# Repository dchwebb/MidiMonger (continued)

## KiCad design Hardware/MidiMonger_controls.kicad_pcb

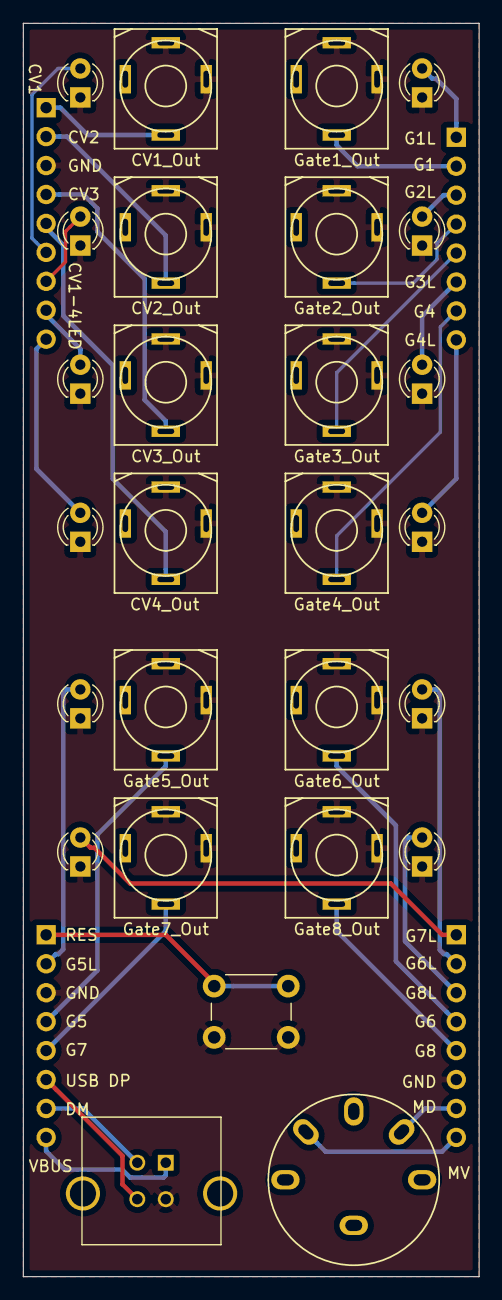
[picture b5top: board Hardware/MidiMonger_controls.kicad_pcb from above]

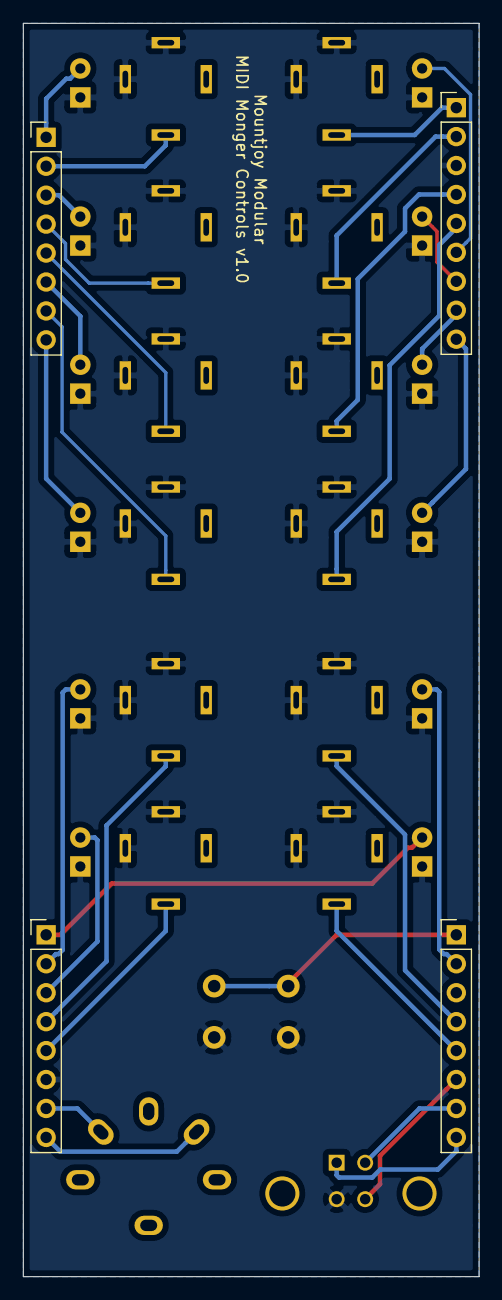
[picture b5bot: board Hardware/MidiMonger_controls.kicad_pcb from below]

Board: 2 copper layers, 40.0 x 110.0 mm, 31 parts (4 on the bottom side), 31 nets.

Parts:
D1: GATE1; LED_D3.0mm
D2: GATE2; LED_D3.0mm
D3: GATE3; LED_D3.0mm
D4: GATE4; LED_D3.0mm
D5: CV1; LED_D3.0mm
D6: CV2; LED_D3.0mm
D7: CV3; LED_D3.0mm
D8: CV4; LED_D3.0mm
D9: GATE5; LED_D3.0mm
D10: GATE6; LED_D3.0mm
D11: GATE7; LED_D3.0mm
D12: GATE8; LED_D3.0mm
J2: Gate3_Out; Cliff_3.5mm_Stereo_Jack
J3: Gate4_Out; Cliff_3.5mm_Stereo_Jack
J4: Gate1_Out; Cliff_3.5mm_Stereo_Jack
J5: Gate2_Out; Cliff_3.5mm_Stereo_Jack
J7: Gate5_Out; Cliff_3.5mm_Stereo_Jack
J8: Gate6_Out; Cliff_3.5mm_Stereo_Jack
J9: Gate7_Out; Cliff_3.5mm_Stereo_Jack
J10: Gate8_Out; Cliff_3.5mm_Stereo_Jack
J11: CV1_Out; Cliff_3.5mm_Stereo_Jack
J12: CV2_Out; Cliff_3.5mm_Stereo_Jack
J13: CV3_Out; Cliff_3.5mm_Stereo_Jack
J14: CV4_Out; Cliff_3.5mm_Stereo_Jack
J15: USB_B_Wurth
J16: MIDI_DIN
J20: Conn_01x09_Female; Socket_Strip_Straight_1x09_Pitch2.54mm
J21, J22, J23: Conn_01x08_Female; Socket_Strip_Straight_1x08_Pitch2.54mm
SW1: SW_Push; SW_PUSH_6mm

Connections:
CV1_LED_OUT: D5.2, J20.6
CV1_OUT: J11.3, J20.1
CV2_LED_OUT: D6.2, J20.7
CV2_OUT: J12.3, J20.2
CV3_LED_OUT: D7.2, J20.8
CV3_OUT: J13.3, J20.4
CV4_LED_OUT: D8.2, J20.9
CV4_OUT: J14.3, J20.5
GATE1_LED_OUT: D1.2, J21.1
GATE1_OUT: J4.3, J21.2
GATE2_LED_OUT: D2.2, J21.3
GATE2_OUT: J5.3, J21.4
GATE3_LED_OUT: D3.2, J21.6
GATE3_OUT: J2.3, J21.5
GATE4_LED_OUT: D4.2, J21.8
GATE4_OUT: J3.3, J21.7
GATE5_LED_OUT: D9.2, J22.2
GATE5_OUT: J7.3, J22.4
GATE6_LED_OUT: D10.2, J23.2
GATE6_OUT: J8.3, J23.4
GATE7_LED_OUT: D11.2, J23.1
GATE7_OUT: J9.3, J22.5
GATE8_LED_OUT: D12.2, J23.3
GATE8_OUT: J10.3, J23.5
GND: D1.1, D2.1, D3.1, D4.1, D5.1, D6.1, D7.1, D8.1, D9.1, D10.1, D11.1, D12.1, J2.1, J3.1, J4.1, J5.1, J7.1, J8.1, J9.1, J10.1, J11.1, J12.1, J13.1, J14.1, J15.4, J20.3, J22.3, J23.6, SW1.2
MIDI_DATA: J16.5, J23.7
MIDI_VREF: J16.4, J23.8
RESET_SWITCH: J22.1, SW1.1
USB_DM: J15.2, J22.7
USB_DP: J15.3, J22.6
USB_VBUS: J15.1, J22.8

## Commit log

2019-10-24 Removed apparently unused code from USB class
2019-10-24 Added handling for monophonic pitch and on/off handling via std::list
2019-10-28 Updates to web editor; added midi handler class
2019-10-30 Implemented basic external DAC support
2019-10-31 dacA data send
2019-11-01 Implemented software/hardware NSS for DAC and moved initialisation to DAC class
2019-11-01 CV out to external DAC
2019-11-04 Updates to configuration message exchange; schematic revised to include gate output
2019-11-05 Editor can now configure CV outputs; fixed USB/MIDIHandler binding
2019-11-07 Switched to MAX5134 DAC; added test for MIDI channel in editor; NB issue in editor intermittently not receiving config from USB
2019-11-07 Added MIDI controller tests
2019-11-08 Fixed bug relating to editor crashes; started implementing polyphonic mode
2019-11-08 Configured additional gates and cv outputs
2019-11-09 Updated schematic
2019-11-15 Updated footprints and added LEDs and additional outputs; added handling for serial MIDI
2019-11-15 Split schematic into control board and electronics board
2019-11-16 First draft of control PCB
2019-11-18 Rough drafts of controls and electronics PCBs
2019-11-19 First completed draft of PCB electronic layout
2019-11-19 Updated silkscreen
2019-11-20 Updated silkscreens and further PCB optimisations
2019-11-22 Panel first draft with components
2019-11-26 First draft of PCBs completed and sent to JLC
2019-12-02 Fixes to polyphonic notes asignment and reorganised editor to reflect hardware layout
2019-12-02 Added pitchbend handling
2019-12-04 Clock handling and tidy up
2019-12-05 Polyphony fixes and clock improvements
2019-12-05 Cleaned up MIDI serial handler
2019-12-18 Created separate project for dev board using CodeIDE
2019-12-20 added outline of config saving
2019-12-20 Further work on config saving
2019-12-20 Added basic config change validator
2019-12-21 Added startup lightshow; minor bug fixes
2020-07-10 Removed old code and tidied up project
2020-07-10 Fixed grounding error with output jacks on controls board
2020-08-01 Switched MIDI endpoints to BULK
2020-08-02 Updates including changes from CDC tests
2020-08-02 USB implementation updated to use CDC test code; added SysEx handling; can now receive USB data in longer than 32 bits
2020-08-02 Imported remaining CDC code and implemented some basic SysEx over USB tests
2020-08-06 Made 3D model of 5 pin DIN
2020-08-08 Merged combined CDC and MIDI USB functionality and simple test
2020-08-09 Added test code to play notes via COM Port; added image of PCB
2020-08-09 Updated image location
2020-08-09 Update image
2020-08-09 Added PCB images
2020-08-09 Added PDF Schematics
2020-08-09 Fixed issue in web editor with channel = 16; added config command to COM interface
2020-08-10 Resized images
2020-08-17 Work on FIFO sizes - appears to now be working correctly with large packets
2020-08-17 Code cleanup - disabled debug code; working on MIDI Monger hardware
2020-08-17 Added configuration options for CV outputs and pitchbend range
2020-08-18 Code refactoring and tidy up; all tested and working; built with -O1 flag
2021-08-22 Clean up schematics
2021-10-13 Updated pictures
2022-02-06 Reinstated accidentally deleted interrupt.h
2022-03-14 Updated to Kicad v6
2022-03-31 Updates to Kicad 6
2022-10-07 Kicad updates
2023-02-28 Added Quad Controls PCB
2023-02-28 Added panel PCB; added board interconnects
2023-03-01 Added inter-board connector
2023-03-02 Cleaned up Panel and Controls
2023-03-02 Fixes to controls board
2023-03-03 Normalised audio to all CV returns
2023-03-31 Updated Midi handling to prevent 'voice-stolen' notes replaying once voices available again
2024-08-01 Copied v2 firmware from F446_USB_Host
2024-08-01 Cleaning up usb device code
2024-08-01 Added option to enable/disable USB device
2024-08-01 Started v2 hardware design
2024-08-02 Updates to PCB layout
2024-08-03 Component PCB first pass routing
2024-08-03 Started Control layout
2024-08-06 Laying out panel
2024-08-07 Hardware layout
2024-08-08 Gerbers prepared for manufacture
2024-08-09 Added additional decoupling capacitors to 5V line
2024-08-17 Updating firmware for v2 hardware
2024-08-17 Refactored DACHandler
2024-08-18 Added configurable offset and scale for DAC
2024-08-21 Fixes to mode switching; added serial MIDI support
2024-08-21 Splitting v1 and v2 hardware into two builds
2024-08-22 Fixing issues with CV type changing and pitchbend
    Clean up project
2024-08-23 Fixed issues managing config
2024-08-25 Fixed v1 conflict with gate 8 and mode switch
2024-09-05 Started adding support for HID class
    Fixed bug in USB host Process state machine in set wakeup feature
2024-09-06 HID class working; reads HID descriptor;
2024-09-06 Implemented very crude HID descriptor parsing
2024-09-08 Added HID descriptor/report parsing
2024-09-09 Updates to report parsing
2024-09-09 Updates to HID class
2024-09-11 Command UI can be accessed over both USB serial and UART
2024-09-11 USB Mouse sends CV and Gate data
2024-09-13 Adding configurable mouse controls
    Altered config handler to resolve global initialisation order issues
    Increased priority of UART interrupts to avoid USB interrupt blocking
2024-09-13 Started adding support for portamento
2024-09-14 Portamento function working
2024-09-15 Changes to voice allocation to allow more modes of operation
2024-09-16 Added v2 hardware pictures
2024-09-16 Updating pictures
2024-09-17 Added schematics
2024-09-18 Updated to new Readme
2025-03-07 Reversed MIDI device/host graphics on panel v2.1
2025-03-07 Fix for MIDI clock interfering with note off
2025-03-09 Fix to usb device under Linux
    EP0In not respecting request length
2025-08-13 Added lightshow for host connection; Code clean-up
2025-08-13 MIDI channel note assignment uses round-robin for polyphonic playing
2025-08-18 Fixes to round-robin assignment; Reset USB core to improve switching from host to device mode
2025-08-19 Reduced clock to 120MHz; fixed pitch bend on released notes
    +12V rail current reduced from 124mV to 102mV
2025-08-20 Code clean up
2025-08-21 Added midi event debug mechanism
2025-08-23 Increase size of debug capture buffer
2025-08-23 MIDI Support for multi word USB host packets
2025-08-23 Fix to multiple USB packet handling
2025-08-23 Updated debug info to ignore Active Sensing and blank messages
2025-08-24 Enhanced debugging for multi/split events
2025-08-24 Handle NoteOn event with velocity = 0 meaning NoteOff
2025-08-24 Added descriptor output to command line; potential support for misc classes
2025-08-25 Increased maximum number of endpoints
2025-08-26 Fixed issue processes USB Misc classes
2025-08-26 Increased maximum configuration descriptor size
2025-08-26 Added tool to output raw config descriptor data
2025-08-27 Test code for processing problem config descriptors
2025-08-27 Removed test code; increased max interface count to 8
2025-08-28 Rewrote note allocation code to avoid using std::list
2025-09-27 Fixes to pitchbend test and led
2025-12-11 Fix skipped notes by correcting channelNotes indexing and handling multi-event USB MIDI packets
